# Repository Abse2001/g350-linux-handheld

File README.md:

# G350 AM3352 Linux handheld — in progress

**Cloud continuation:** start with [the complete handoff](docs/CLOUD_HANDOFF.md),
[the original user-visible chat](docs/CHAT_CONTEXT.md) and [AGENTS.md](AGENTS.md).
The full authored project and hash-indexed ignored routing evidence are preserved;
restore with `python3 scripts/restore-cloud-evidence.py`. Ubuntu cloud setup is
`bash scripts/setup-cloud.sh`, followed by `source cloud/env.sh` in each shell.
The checked default is still the eleven-signal byte0 subset. Latest byte1 source
replays and native failures are preserved separately; their aggregate/remaining
independent checks are pending. This transfer does not make the PCB order-ready.

The selected processor is a **bare TI AM3352BZCZ100**, directly on the main PCB, with **512 MB Micron MT41K256M16TW-107:P DDR3L** operated in DDR3-compatible mode. The user chose AM3352 for simple games rendered by the CPU; a 3D GPU is no longer required. The design is authored in **tscircuit**, using individually imported JLCPCB components. No complete SBC or processor module is imported.

**The integrated handheld is not ready to fabricate or order.** The current checked routing entry is [`experiments/am3352-g350-byte0-complete-bus.circuit.tsx`](experiments/am3352-g350-byte0-complete-bus.circuit.tsx): **280 placed components, four copper layers, a 76 × 118 mm shaped outline and 1.6 mm nominal thickness**. The lower speaker tab is 22 mm wide with a 19 mm extension. This routing entry and its CPU/RAM power replay both match the shared mechanical geometry; run `node scripts/check-g350-mechanical-envelope.mjs` to check them. These are provisional dimensions inside the published exterior envelope; mounting posts, shell ribs and button/port alignment remain unmeasured. The default `index.circuit.tsx` now opens this current shaped handheld. Older 212-component routing fixtures remain historical experiments; their channel counts do not qualify this layout. DDR and other critical routing, Linux provisioning and original-shell fit remain unfinished. The fabrication exporter remains blocked by `design-status.json`.

On the current shaped board, **all 101 CPU/RAM ground and DDR supply terminals** reach their correct filled reference planes through 97 physical vias. **All eleven byte0 signals** use native `bus_lanes` carriers and manually repaired routes, with their complete source-bus definition restored. Byte0 planar skew is **0.207792 mm against 0.635 mm**; strobe-pair skew is effectively zero against 0.127 mm. Numeric-pad connectivity, all-layer Gerber shorts and independent physical DRC pass for this subset. The source has **112 traces and 119 standard through-vias**. There are **38 DDR signals to route**, 403 silkscreen warnings, 818 open-port errors and 108 missing-trace errors. Bypass loops, complete timing and stackup impedance remain unqualified. [Current routing checks](checks/integrated/g350-byte0-complete-bus/check-summary.json), [bottom snapshot](checks/integrated/g350-byte0-complete-bus/g350-byte0-bottom.png), [routing notes](docs/G350_CURRENT_DDR.md). The separate byte1 experiment now has 22 manual package escapes with zero native geometry errors. Its native `bus_lanes` carrier attempt exhausted the strobe-pair search budget; the actual-source fanout replay returned the cached escapes but its implicit completion stage exceeded the external deadline. No completed byte1 source or new connected signals are qualified; the checked default is preserved. [Experimental findings](checks/integrated/g350-ddr-bootstrap/byte1-package-access-findings.json).

The completed handheld must have eleven front buttons, an FPC display, an onboard microSD holder and one USB-C connector for charging and data/provisioning. Components and copper routing are allowed on both sides. There are no analog sticks or rear buttons.

The historical command package-access study independently verifies **all 48 CPU/RAM pad-to-via exits for the 24 command/control signals**, while retaining both data bytes, reset and the clock pair. Shorts, copper/drill clearance and filled RAM reference checks pass. The diagnostic has 25 retained complete DDR channels, 48 dangling terminal-via warnings and 24 unfinished commands. Subsequent phased native routing plans six carriers; manual repair plans five more, leaving 13 unresolved. These carriers still need a combined editable replay and independent checks. The best checked complete-signal subset remains DDR42. [Package-exit evidence](checks/integrated/am3352-command-compatible-fanouts-802-check-summary.json). Fabrication remains blocked; no remote publication was made.

The latest separate **DDR42 checkpoint connects 42/49 DDR signals**, with 144 trace pieces and 187 full-depth through-vias. Independent numeric-pad connectivity, all-layer Gerber shorts and physical clearance/drill checks pass. Both byte groups and all three differential pairs pass relative planar skew. **Seven signals remain open:** A3, RASn, WEn, A2, A12, A11 and CKE. Seventeen command/clock nominal lengths and seven reduced-spacing exposures need repair; complete DDR timing and signal integrity remain unqualified. The updated `bus_lanes` phase preserves the fixed copper and physical pads but has no complete new output. [Checked evidence](checks/integrated/am3352-command-fine-782-replay-check-summary.json), [editable replay](experiments/am3352-command-fine-782-replay.circuit.tsx), [native phase entry](experiments/am3352-command-fine-782-replay-native-phase.circuit.tsx). At that historical checkpoint the default stayed DDR30; fabrication remains blocked.

The previous spacing-repaired **copper checkpoint connects 33/49 DDR signals**, with 135 trace pieces and 169 through-vias. A guarded wire-only D12 shortcut repairs its reduced class-spacing exposure from **32.176112 mm to 28.195190 mm**, within the **31.75 mm allowance**, without changing any holes or other routes. D12 is **50.983197 mm**; byte0/byte1 relative skews are **0.157421/0.496669 mm** and all three pairs retain their relative limits. Fresh native DDR/USB/filled-reference connectivity, all-layer Gerber shorts and physical DRC pass, with 418 presentation warnings, 499 reported/capped host opens and recorded ignored checks. **Sixteen DDR signals remain open**; CK/CKn/CKE/A3/A6 nominal repairs and complete spacing, impedance, return-path, termination and timing qualification remain required. [Checked copper](checks/integrated/am3352-ddr-usbc-d12-spacing-repaired-check-summary.json), [partial spacing audit](checks/integrated/am3352-ddr33-d12-repaired-class-spacing.json), [top](images/am3352-ddr-usbc-d12-spacing-repaired-top.png) and [bottom](images/am3352-ddr-usbc-d12-spacing-repaired-bottom.png). Revalidate with `npm run check:ddr-d12-spacing-evidence` and `npm run check:ddr-class-spacing`. That historical checkpoint retained the 30/49 default; fabrication remains blocked.

A separate **bottom-side RAM placement study** retains all 212 host components, 912 pads and 49 logical DDR connections. RAM references and shared USB-C copper pass fresh independent checks on four layers; fourteen small RAM bypass capacitors move to top, and all 89 existing holes remain standard 18/10 mil through-vias. DDR is entirely unrouted in this study. Native all-channel and ordered-fanout trials **704–709** prepare real endpoints but have no complete output; no partial routes are promoted. An initial eight-USB-via size failure is retained as rejected evidence, followed by a corrected, checked rebuild. [Placement checks](checks/integrated/am3352-ram-bottom-via-style-corrected-check-summary.json), [seven bound terminal trials including D12 repair 703](checks/integrated/am3352-ddr33-d12-ram-bottom-trial-status.json). Revalidate with `npm run check:ram-bottom-evidence` and `npm run check:ddr-d12-ram-bottom-trials`.

The newer bottom-RAM replay has **28/49 connected DDR signals**, comprising **19 retained native bus-lane paths and nine manual paths**. All original 102 host/USB/reference trace pieces and 89 physical holes remain exact; this candidate has 130 trace pieces and 129 through-vias. Independent numeric-pad DDR/USB and filled-reference connectivity, all-layer shorts and physical DRC pass. **21 DDR signals remain open**, both byte groups are incomplete, and command matching/nominal lengths remain unqualified. Its separate placement-derived command target is **40.62 mm**; this does not change the top-RAM target. All 28 connected paths pass the partial reduced-spacing exposure limit, with a maximum of 31.421059 mm; complete spacing and signal integrity remain unchecked. A selected-terminal-via search-model bug was corrected and regression checked. The unsolved native run is retained as provenance, rather than represented as a solved 49-channel output. [Checked replay](checks/integrated/am3352-ram-bottom-flexible-fanout-747-replay-check-summary.json), [electrical review](checks/integrated/am3352-ram-bottom-flexible-fanout-747-replay-spacing-and-nominal-review.json), [38 terminal trials](checks/integrated/am3352-bottom-manual-trial-status.json), [top](images/am3352-ram-bottom-flexible-fanout-747-replay-top.png) and [bottom](images/am3352-ram-bottom-flexible-fanout-747-replay-bottom.png). That historical study retained the 30-signal default and separate 33-signal checkpoint. Nothing was pushed or released for ordering.

The earlier **A6 copper bootstrap connects 32/49 DDR signals** in one source, with 134 trace pieces and 163 through-vias. It supplies the checked prior geometry for the CASn replay. Its A6=51.715840 mm and A3=45.411583 mm nominal failures remain required repairs. [Prior scoped checks](checks/integrated/am3352-ddr-usbc-a6-bootstrap-check-summary.json); `npm run check:ddr-a6-bootstrap-evidence`.

The earlier **A3 copper bootstrap connects 31/49 DDR signals**, with 133 trace pieces and 161 through-vias. It preserves every checked DDR30 trace and hole. Native DDR/USB/reference connectivity, all-layer shorts and physical DRC pass, but **A3=45.411583 mm fails the nominal range**. The wire-only shortcut search could not bring it into range. This checkpoint supplies the checked prior copper for the separate A6 replay. [A3 bootstrap checks](checks/integrated/am3352-ddr-usbc-a3-bootstrap-check-summary.json). Revalidate with `npm run check:ddr-a3-bootstrap-evidence`.

Earlier DQM1/D10 access trials routed native CASn and CSn0 but could not restore the two data routes. Those incomplete stages remain non-exportable and are superseded by the complete D3-coupled replay above. [Historical bound trials](checks/integrated/am3352-ddr32-casn-neighbor-replan-trial-status.json); `npm run check:ddr-casn-neighbor-replan-trials`.

The board must **fit the original G350 shell**. Its listed 81 × 128 × 22 mm outside dimensions do not establish the internal PCB outline. The working G350 outline is **76 × 118 mm**, with chamfered corners and a lower speaker tab; see the [dimensioned drawing](mechanical/g350-provisional-outline.svg). The nominal centered margins from the outside case are 2.5 mm per side and 5 mm per end; the USB-C assembly courtyard projects 0.651 mm past the top PCB edge. These are engineering allowances, not measured internal clearances or a verified original-board replacement. The historical 100 × 124 mm routing fixture does not fit the case and is not the mechanical target. Original screw posts, button centers, port openings and assembly clearances still require verification. [Shell-fit requirements](docs/G350_SHELL_FIT.md).

The historical DDR30 default was `experiments/am3352-ddr-usbc-wen-nominal.circuit.tsx`: **30/49 DDR signals connected**, with **132 trace pieces and 157 through-vias**. A native `bus_lanes` WEn carrier inside the DDR reference bounds and guarded manual package fanouts give **WEn=43.228641 mm**, within the placement-derived 41.75–44.29 mm nominal range. Every checked DDR29 trace and hole remains unchanged. A5 remains **43.020000 mm**, CSn0 **42.800714 mm**, ODT **43.018281 mm** and D14 **50.919109 mm**. Both bytes and all three differential pairs retain their checked relative planar limits. Exact native DDR/USB/reference connectivity passes, with zero all-layer Gerber shorts and reported physical DRC violations, 418 presentation warnings and 499 reported/capped host opens. All 18 RAM supply balls, 21 ground balls and 28 bypass terminals reach the connected filled reference planes. Configured ignored native checks remain recorded. CKE/clock nominal lengths still fail; the **19 remaining address/control signals**, full command matching, package/via delays, coupling/impedance, powered host/Linux and original-shell fit remain unqualified. [Checked evidence](checks/integrated/am3352-ddr-usbc-wen-nominal-check-summary.json); [top](images/am3352-ddr-usbc-wen-nominal-top.png) and [bottom](images/am3352-ddr-usbc-wen-nominal-bottom.png) snapshots. Revalidate with `npm run check:ddr-wen-evidence`. Earlier candidates below are historical evidence.

The historical DDR28 replay is `experiments/am3352-ddr-usbc-csn-joint.circuit.tsx`: **28/49 DDR signals connected**, with **130 trace pieces and 149 through-vias**. A native `bus_lanes` CSn0 carrier and guarded manual package fanouts add **CSn0 at 42.800714 mm**, within the placement-derived 41.75–44.29 mm nominal range. D10 remains unchanged; only D14's CPU prefix is repaired with two vias, giving **D14=50.919109 mm**. All 147 old holes and the other 128 traces remain unchanged. Byte0/byte1 skews remain **0.157421/0.635000 mm**; DQS1/CK skews remain **0.079409/0.076616 mm** against 0.127 mm. Exact native DDR/USB/reference connectivity passes, with zero all-layer Gerber shorts and reported physical DRC violations, 418 presentation warnings and 499 reported/capped host opens. All 18 RAM supply balls, 21 ground balls and 28 bypass terminals reach the connected filled reference planes. The configured ignored native checks remain recorded. CKE/clock nominal lengths still fail; the **21 remaining address/control signals**, complete command matching, package/via delays, coupling/impedance, powered host/Linux and original-shell fit remain unqualified. [Checked evidence](checks/integrated/am3352-ddr-usbc-csn-joint-check-summary.json); [top](images/am3352-ddr-usbc-csn-joint-top.png) and [bottom](images/am3352-ddr-usbc-csn-joint-bottom.png) snapshots. Revalidate with `npm run check:ddr-csn-evidence`.

The historical unmatched **26/49 DDR continuity candidate** adds CKE using a native bus_lanes channel and manually repaired RAM fanouts. All exact DDR/USB and RAM reference connections pass, with zero all-layer shorts and physical DRC violations. A bounded DDR power-plane clearance change restores the RAM supply island while preserving manufacturing minimums and plane boundaries. **DQS1 and byte1 skew still fail at 10.167587/10.584847 mm**, and CKE is longer than the current placement-derived nominal range. This earlier candidate remains separate from the repaired default. [Scoped evidence](checks/integrated/am3352-ddr-usbc-cke-joint-power-plane-bounded-check-summary.json); [top](images/am3352-ddr-usbc-cke-joint-power-plane-bounded-top.png) and [bottom](images/am3352-ddr-usbc-cke-joint-power-plane-bounded-bottom.png) snapshots. Revalidate with `npm run check:ddr-cke-joint-plane-evidence`.

The historical separate **25/49 DDR continuity trial** restores both strobes around a freshly routed native `bus_lanes` clock pair. All 25 exact CPU/RAM pad pairs, shared USB-C copper and RAM plane/bypass connections pass independent checks, with zero physical DRC violations and all-layer Gerber shorts. The clock pair passes its 0.127 mm planar limit at **0.076616 mm**. **Strobe and whole-byte1 matching still fail at 7.145626 mm**; strobe via counts are also unequal. This 127-trace/137-via trial does not replace the checked default. Its 24 address/control signals, full electrical timing, complete host and measured original-shell layout remain unfinished. [Scoped checks](checks/integrated/am3352-ddr-usbc-clock-strobes-unmatched-check-summary.json); [editable source](experiments/am3352-ddr-usbc-clock-strobes-unmatched.circuit.tsx); [top](images/am3352-ddr-usbc-clock-strobes-unmatched-top.png) and [bottom](images/am3352-ddr-usbc-clock-strobes-unmatched-bottom.png) snapshots. Revalidate with `npm run check:ddr-strobe-evidence`.

The newest coordinated diagnostic preserves eleven byte0 channels and independently verifies all **74 remaining byte1/command escape terminals** around them. All-layer shorts and clearance violations are zero, and RAM plane connections pass. Those reservations add no complete channels; byte0 length matching still fails, and dangling copper remains. The separately matched byte1 candidate has not been merged. [Combined reservation checks](checks/integrated/am3352-ram-rotated-180-byte0-fixed-reused-reservations-check-summary.json).

A newer whole-byte-swap alternative routes all eleven byte0 channels with **24 DDR vias**. Independent pad/plane connectivity, shorts and physical DRC checks pass, but whole-byte skew still fails at 13.889 mm against 0.635 mm. Native preparation can reserve the remaining 74 terminals around that copper; byte1 routing remains incomplete. This separate candidate does not replace or add channels to the default layout. [Swapped-byte checks](checks/integrated/am3352-ram-rotated-180-byte-swapped-byte0-pair-check-summary.json).

A separate **212-component USB-C source draft** now adds the shared charging/data socket, USB0 ESD protection, independent CC pull-downs and a VBUS sensing filter/clamp. Generated connections and all 36 exported USB numeric-pad assignments pass. Its existing eleven DDR channels and RAM plane connections pass fresh native checks; shorts and physical DRC violations are zero. **USB traces, charger current policy, VBUS temperature/transient limits and Linux provisioning remain unfinished**, along with the measured original-shell layout. No finished board was imported. [USB-C checks](checks/integrated/am3352-usbc-device-check-summary.json); source: `experiments/am3352-usbc-device-source.circuit.tsx`.

The newer **USB copper replay** routes data from the CPU through ESD protection to both connector orientations, both CC/Rd connections, local VBUS bypass and ground returns. Native `bus_lanes` supplies the pair/CC bootstrap; manual connections and tuning supplement it. Fresh source, KiCad connectivity, physical DRC and all-layer shorts checks pass. Both data orientations have **0.0635 mm planar skew**, with equal via counts within each orientation. The replay adds 23 trace pieces and 12 through-vias while preserving its eleven DDR channels. **The PMIC VBUS feed, CPU VBUS sensing, controlled impedance, current policy, remaining DDR/host routing, Linux provisioning and shell fit remain unfinished.** This candidate remains separate from the default 23-channel DDR source. [Routed USB checks](checks/integrated/am3352-usbc-routed-check-summary.json), [editable source](experiments/am3352-usbc-routed-replay.circuit.tsx), [PCB snapshot](images/am3352-usbc-routed-top.png).

## DDR routing workflow

The [tscircuit DDR routing guide](https://docs.tscircuit.com/guides/routing-ddr) was rechecked on 2026-10-04, including the complete AM3352 example. The native preset is `autorouter="bus_lanes"`. The default circuit uses this preset to generate local dogbones and route the channel. Manual fanouts, placement changes and local trace repairs may supplement it when needed; successful copper still requires independent checks.

The new fixture declares **49 actual shared DDR signals**, two 11-signal byte buses, a 26-signal command/clock timing group, and separate reset. It declares both DQS differential pairs and the CK pair. The 4 Gb x16 memory uses A0–A14; its M7 is NC. CPU DDR_A15 is therefore unused. Numeric port selectors avoid collisions between RAM ball labels such as A3 and address-function aliases with the same name.

All **324 CPU and 96 RAM balls**, functions and nominal 0.8 mm grids have been checked against the manufacturer documents. The supplier import's incomplete CPU aliases and malformed RAM aliases were corrected. CPU pads use TI's 0.4 mm example lands; RAM pads use the Micron TW drawing's 0.42 mm lands. This is a nominal geometry/function check, not complete solder-mask or assembly qualification. See `checks/integrated/am3352-import-validation.json`.

The historical repaired-strobe source connects **25/49 DDR signals**: both complete byte lanes, reset and CK/CKn. Byte0 uses bottom, byte1 top, and inner1 GND/inner2 DDR power remain reference planes. Manual RAM strobe escapes supplement the native bootstrap. Removing a redundant inward CPU/channel turn shortens DQS1 from 53.720144 to 50.953139 mm; DQSn1 is 51.001321 mm. Every other route of the checked clock source remains unchanged. Both bytes, both DQS pairs and CK pass their separate planar limits, while the complete command/clock group correctly fails because its 24 address/control signals are open. All 25 exact CPU/RAM pad pairs are independently verified in KiCad. This does not qualify full electrical timing or fabrication.

A separate fresh native bootstrap now reserves all **96 CPU/RAM breakouts for all 48 synchronous DDR signals together**, retaining the original power copper and four-layer limit. KiCad verifies all 96 pad-to-via connections and the RAM plane/bypass connections. Gerber shorts and clearance errors are zero; all 96 unfinished-via warnings remain. This creates no new complete channel and does not replace the checked 23-signal default. [Joint breakout checks](checks/integrated/am3352-joint-native-breakout-check-summary.json).

The next separate trial has **all 52 natural command/clock fanouts connected to their exact CPU/RAM pads**, with zero all-layer shorts and clearance errors. Its 47 dangling-via and 44 dangling-track warnings remain. [Natural fanout checks](checks/integrated/am3352-natural-command-fanouts-check-summary.json).

A terminal-via diagnostic also passes all 52 pad-to-terminal checks with zero all-layer shorts and clearance violations. It retains 96 dangling-via warnings and completes no new DDR channel. The current repair uses only four added clock-terminal vias, the native `bus_lanes` clock bootstrap and temporary manual bridges on top/bottom. Command-bus crossings and original timing limits must pass before accepting any routes. [Terminal checks](checks/integrated/am3352-dual-layer-command-terminal-check-summary.json).

The separate command/clock replay now connects **all 26 command signals**. Native `bus_lanes` supplies the bootstrap and two clock channels; manual fanout/channel repairs and A2 loop cleanup supplement it. The actual tscircuit source passes all-layer shorts and independent KiCad pad connectivity, RAM reference connectivity and physical DRC at every severity. It has 95 trace pieces and 199 through-vias. **Length matching still fails:** command skew is 53.182 mm against 0.635 mm, and clock skew is 2.898 mm against 0.127 mm. Its two bytes and reset are open. A merge screen finds five via/hole conflicts with the active byte routes, so these separate results do not make a 49-signal DDR board. [Command checks](checks/integrated/am3352-command-unmatched-pruned-check-summary.json), [editable replay](experiments/am3352-command-unmatched-pruned-replay.circuit.tsx).

The newer command-first diagnostic verifies all **44 native CPU/RAM byte breakouts** against that command copper, with zero all-layer shorts and clearance violations. It preserves all 26 command channels but adds no complete byte channel. Its 22 dangling-via and 22 dangling-track warnings remain. A separate local-access trial opens WEn, RASn and ODT to plan compatible byte routing; those nets still require complete rerouting and matching. [Byte-breakout checks](checks/integrated/am3352-command-first-native-byte-check-summary.json).

An earlier placement trial rotates RAM by **180°**, with explicitly transformed and checked supply escapes. Its joint native bootstrap verifies all 96 synchronous pad-to-terminal connections and preserves all 39 RAM supply/ground and 28 bypass-plane connections. The pruned reservation retains 74 dangling-via and 22 dangling-track warnings and adds no complete channel. [Rotated breakout checks](checks/integrated/am3352-ram-rotated-180-pruned-breakout-check-summary.json).

A separate editable replay of that placement now connects **all eleven byte0 signals through native `bus_lanes` channels and manual fanouts**. Actual tscircuit and KiCad checks confirm zero all-layer shorts, zero physical DRC violations, and preserved RAM plane connections. DQS skew is zero, but whole-byte skew is **16.105 mm against 0.635 mm**. It has 80 trace pieces and 99 through-vias; 38 DDR signals remain open. This candidate is separate from the active 23-signal layout, and routes from the old RAM orientation cannot be combined with it. [Rotated byte0 checks](checks/integrated/am3352-ram-rotated-180-byte0-pair-check-summary.json), [editable replay](experiments/am3352-ram-rotated-180-byte0-pair-replay.circuit.tsx).

## Build and verify

Versions reverified against the registry on 2026-10-05: **tscircuit 0.0.2744**, **tsci CLI 0.1.2237**, **capacity-autorouter 0.0.958**, and **core 0.0.2088**, **props 0.0.687** and **checks 0.0.239**. The project pins one core version, Circuit JSON 0.0.515 and React 19.3.0 so clean installs load compatible peers. Both lockfiles are synchronized; use `bun install --frozen-lockfile` or `npm ci --legacy-peer-deps`. The selected byte0 phase completes and typechecking and all-layer Gerber shorts pass. The whole-board build still reports its unfinished connections. The latest core audit preserves all physical records outside the explicitly reviewed D3 bend and sub-picometre handoff-coordinate repairs, and restores all eleven byte0 bus members. Previously checked circuit/board files remain fixed evidence. [Current upgrade and source checks](checks/integrated/g350-byte0-complete-bus/core-upgrade-and-bus-check.json).

Run direct CLI commands with **`node_modules/.bin/tsci`**; npm scripts already select the project binary. The shell's older global `tsci` reports runtime 0.0.2444 and omits the microSD keepouts in KiCad exports. Affected new exports and shorts checks were rerun with the project CLI. Latest-project-CLI builds reproduce every non-metadata record of both new clock/strobe replays; frozen earlier source snapshots remain intact.

```sh
npm ci --legacy-peer-deps
npm run typecheck
npm run check:am3352-imports
npm run check:am3352-swizzle
npm run build:host-netlist
npm run check:power-netlist
npm run check:boot-netlist
npm run check:storage-netlist
node_modules/.bin/tsci build index.circuit.tsx --disable-parts-engine --autorouter-phase G350_BYTE0_MATCHED --autorouter-timeout 180s
npm run check:memory-connectivity
npm run check:shorts
```

The legacy peer option is required by the current upstream packages' circuit-json peer versions. All-layer Gerber shorts, full signal connectivity, end-to-end skew measurements and independent KiCad copper/drill checks must be run on actual exported AM3352 copper. The completed handheld requires fresh checks after power and peripherals are integrated.

`build:host-netlist` disables automatic routing. Source audits accept only the exact documented package reference escapes and bypass loops, including same-net drill separation; they do not approve arbitrary copper. The checks cover voltage domains, power/reset controls, internal-output isolation, DDR VREF/VTP/ZQ, bypass placement, boot straps and the actual microSD pinout/keepouts. The current shaped-board DDR audit reports eleven connections and still fails on 38 open signals. The historical DDR30 audit fails on 19 open signals; the latest separately checked DDR42 replay has seven opens and still fails command nominal lengths and reduced-class spacing. Both completed byte groups pass their relative planar and physical checks. Remaining host copper and full electrical qualification are unfinished. The partial physical summary rejects copper/drill violations even when KiCad reports them as warnings.

## Repositories and records

- [GitHub](https://github.com/Abse2001/g350-linux-handheld)
- [tscircuit: AM3352 experimental source v1.3.3](https://tscircuit.com/abse/g350-linux-handheld?version=1.3.3-integrated-experimental)
- [Current integrated-host record](docs/INTEGRATED_HOST.md)
- [Historical RK3566 host investigation](docs/RK3566_HOST_RECORD.md)
- [Historical RK3566 memory experiments](docs/RK3566_MEMORY_EXPERIMENTS.md)
- [Historical Revision B carrier](docs/REV_B_CARRIER.md)

Work remains local; GitHub and tscircuit are pushed only on a meaningful breakthrough, as requested. Registry publication is not fabrication approval. `tsci push` ignores `.gitignore`; use the tracked source allowlist in `scripts/stage-registry-source.mjs` and verify every published file hash. Reference PDFs, temporary files and historical manufacturing archives are excluded.

Historical RAM180 milestone: a separate RAM180 replay connects **all eleven byte1 signals**, using native `bus_lanes` channels and manually tuned local fanouts. Actual tscircuit and independent KiCad checks pass shorts, copper/drill clearance, correct numeric pad connectivity and every RAM supply/ground/bypass connection. Whole-byte planar skew is **0.000759 mm against 0.635 mm**, and strobe skew is effectively zero against 0.127 mm. This replay has 81 trace pieces and 111 through-vias. Its other 38 DDR signals remain open; full host routing, impedance, Linux startup and original-shell fit are unfinished. It is not order-ready. [Editable replay](experiments/am3352-ram-rotated-180-byte1-matched-replay.circuit.tsx), [checks](checks/integrated/am3352-ram-rotated-180-byte1-matched-check-summary.json), [snapshot](images/am3352-ram-rotated-180-byte1-matched-top-detail.png). Revalidate with `npm run check:rotated-byte1-matched-evidence`. Other candidate channel counts cannot be added to this result.

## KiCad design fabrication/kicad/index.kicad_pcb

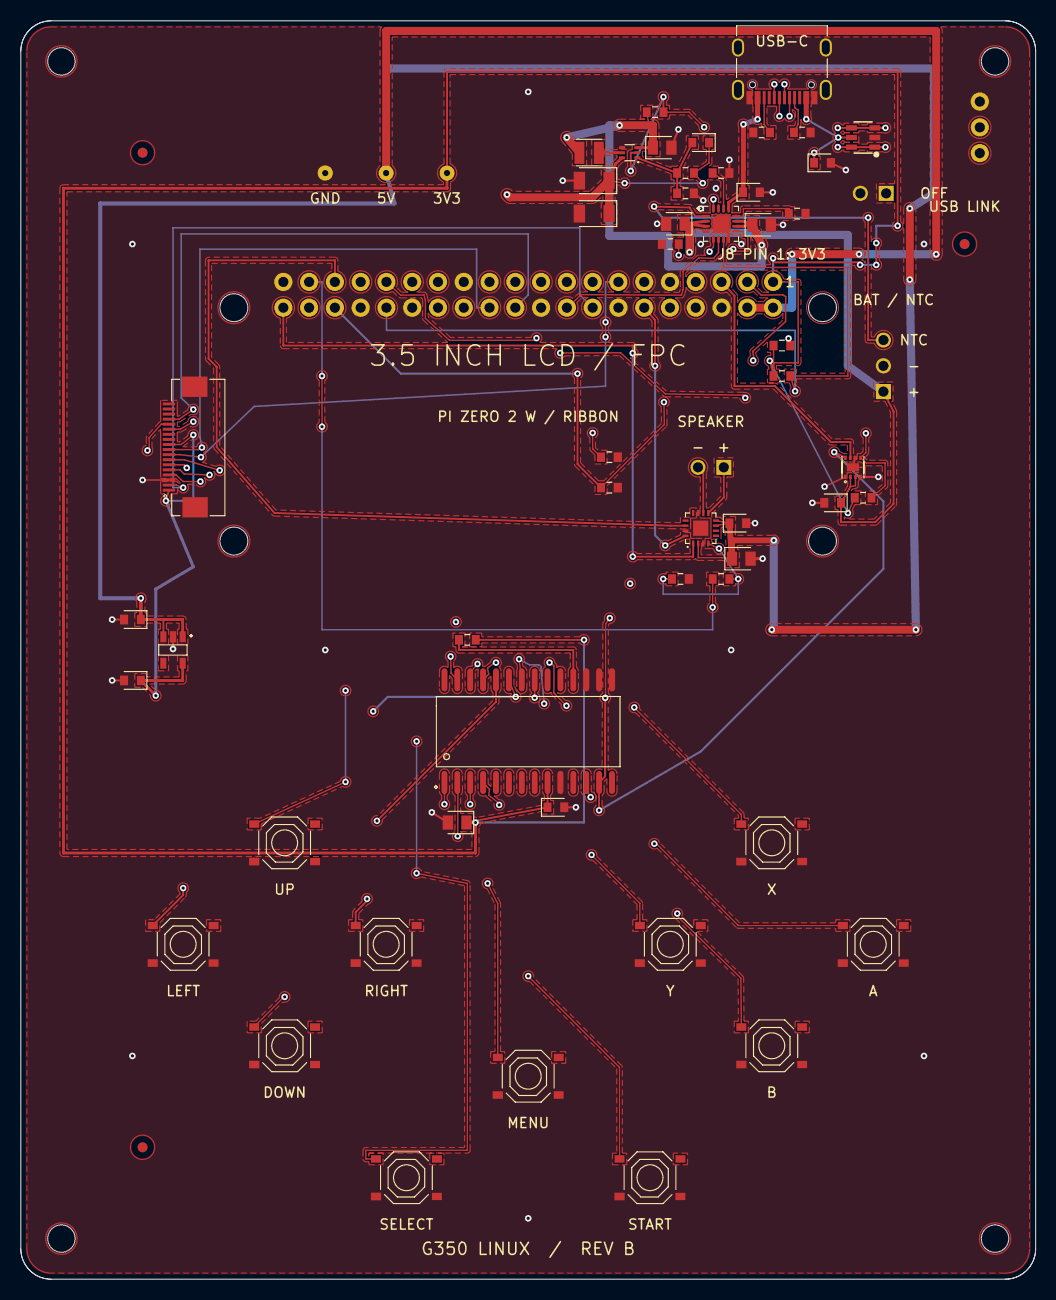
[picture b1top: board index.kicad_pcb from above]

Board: 4 copper layers, 100.0 x 124.0 mm, 60 parts (0 on the bottom side), 52 nets.

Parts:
C_AUDIO_BULK: 10uF; g350_C_AUDIO_BULK_6c8053e0121015ff486027e25d2f9a3d
C_AUDIO_HF: 100nF; g350_C_AUDIO_HF_4f8718706f1c09302dbf2ad0139db390
C_BAT: 10uF; g350_C_BAT_47d06ae03787dae1491fdf5e36386663
C_BOOST_IN: 10uF; g350_C_BOOST_IN_5255146047f73ebf3d99691e333b937d
C_BOOST_OUT1: 22uF; g350_C_BOOST_OUT1_7e38f91c406a288400f2b5dc424f943c
C_BOOST_OUT2: 22uF; g350_C_BOOST_OUT2_1b885d80651f5cbf1a38e902666ed13d
C_FEEDFORWARD: 220pF; g350_C_FEEDFORWARD_16c584a07135c2813459ff9e26163e43
C_GAUGE: 100nF; g350_C_GAUGE_07aee08077a9654108fe54fe7659f0c3
C_KEYS: 100nF; g350_C_KEYS_644960c23e17dcbe1f86e5c27d25a842
C_KEYS_BULK: 10uF; g350_C_KEYS_BULK_468ee6ca3a2664ea2dbde30a2155612a
C_LCD_IN: 1uF; g350_C_LCD_IN_5be2f4460c8d09ba74fd07ba2292fa46
C_LCD_OUT: 1uF; g350_C_LCD_OUT_796ff1802c1fd09f2e506d42773f54dd
C_SYS: 10uF; g350_C_SYS_08f8654077af54ff07a8f0c278fec97d
C_USB: 1uF; g350_C_USB_6f7d3200112a883f6e2dbd821279fcbd
C_USB_ESD: 100nF; g350_C_USB_ESD_55af1c004fe0a61f0a8f97c264ffd5a3
J_BAT: J_BAT; g350_J_BAT_1c1b67e03e54d601673aec1e0ccaae3d
J_LCD: FPC-05F-18PH20; g350_J_LCD_023284580e9b06381b038818276c09f8
J_OFF: J_OFF; g350_J_OFF_72356f40335a52df2715eb027e79d71d
J_PI: 2x20 2.54mm GPIO ribbon header; g350_J_PI_45b957de51d6aa22169953de7f0951de
J_SPEAKER: J_SPEAKER; g350_J_SPEAKER_3187528028e8eb617ca6d6be223698dd
J_USB: TYPE-C-31-M-12; g350_J_USB_2a17ef222ac30dde7f9e0ade2b86f822
J_USB_LINK: J_USB_LINK; g350_J_USB_LINK_151b40200abd6a7f005f94de09fe40c3
L_BOOST: 1µH; g350_L_BOOST_162d00c0709d3ea134f2837e257dba63
R_ALERT_PULL: 100kΩ; g350_R_ALERT_PULL_3ed784801b98b9617608f7422f86cadd
R_AUDIO_EN: 1kΩ; g350_R_AUDIO_EN_00256ea05a4acf414b44f2de0f2b4b03
R_AUDIO_PD: 100kΩ; g350_R_AUDIO_PD_59fa59004b95691f0edad4c2694b12a3
R_CC1: 5.1kΩ; g350_R_CC1_1675a34070e5e12134a9e0fe25c65ce3
R_CC2: 5.1kΩ; g350_R_CC2_70956ae034fa573f2575e6a27fe62483
R_CHG_PULL: 100kΩ; g350_R_CHG_PULL_7cb2e42028dcddff31935fe273fc623d
R_EN: 100kΩ; g350_R_EN_2bedbaa0536a8b212d3d2f1e521b16a3
R_FB_HI: 732kΩ; g350_R_FB_HI_577e14c02929a57f562ea0422a7919fd
R_FB_LO: 100kΩ; g350_R_FB_LO_1fea8fa05f6db621213a041e5e1e41a3
R_GOOD_PULL: 100kΩ; g350_R_GOOD_PULL_2f2dc0202b427dc17a4d445e1fdd067d
R_ILIM: 3.3kΩ; g350_R_ILIM_21d596405ed223ff208621c26021987d
R_ISET: 3.3kΩ; g350_R_ISET_2238e4a07ca9228128e69f9e31899e43
R_RESET: 10kΩ; g350_R_RESET_1a8653a074f691813099309e29d70d43
R_TIMER: 68kΩ; g350_R_TIMER_7999bf001f29811f3b46bcc26a49055d
R_USB_EN1: 100kΩ; g350_R_USB_EN1_2d820ae02cee330178a18f1e1e31513d
R_USB_EN2: 100kΩ; g350_R_USB_EN2_18011b8072715961331e68be2751d523
SW_A: SW_A; g350_SW_A_69607ec017473b7f68110a421896affd
SW_B: SW_B; g350_SW_B_732329a00c351c2174729e1e0ae5a7a3
SW_DOWN: SW_DOWN; g350_SW_DOWN_66fbc8fa73644ada7fccccba73cab166
SW_LEFT: SW_LEFT; g350_SW_LEFT_093028fc1598aadc22012cbc2e69ae9c
SW_MENU: SW_MENU; g350_SW_MENU_4553bc603b53fddf440447e23ca3725d
SW_RIGHT: SW_RIGHT; g350_SW_RIGHT_2a1c1df636849fd642ed21b64f55a396
SW_SELECT: SW_SELECT; g350_SW_SELECT_69cf658e5d66e3ae50fe61ce4495dfee
SW_START: SW_START; g350_SW_START_4c2facc034780d7f4ae0384235c781fd
SW_UP: SW_UP; g350_SW_UP_0f36f6001b9f77e02807f9c034707ba0
SW_X: SW_X; g350_SW_X_35f9e5604aadd4df34aa70e24bfd495d
SW_Y: SW_Y; g350_SW_Y_59763d0027317d3f5826c8822880f1bd
TP_3V3: TP_3V3; g350_TP_3V3_7afe24202a919dff2fde9fe275b1223d
TP_5V: TP_5V; g350_TP_5V_19c1e4e0743222c1315d9f5e29129e83
TP_GND: TP_GND; g350_TP_GND_1bb7c0407627fe212f67c3fe2b0879e3
U_AUDIO: MAX98357AETE+T; g350_U_AUDIO_22ebc3c07d5c01a12833c07e323c7d63
U_BOOST: TPS61023DRLR; g350_U_BOOST_1f3f53c079af91a12be0307e2e900d63
U_CHARGE: BQ24074RGTR; g350_U_CHARGE_5486e04005e95da160599b824536269d
U_GAUGE: MAX17048G+T10; g350_U_GAUGE_1b637ee075d3bcc12fbc055e2ab43883
U_KEYS: MCP23017-E/SO; g350_U_KEYS_647741a01ae1042165c6b61e19918fa3
U_LCD_PWR: AP2112K-3.3TRG1; g350_U_LCD_PWR_6bb0e2e01140a4ff492f98e25c60293d
U_USB_ESD: USBLC6-2SC6; g350_U_USB_ESD_7ae7b8e0673f34e15396b0e23fee2ce3

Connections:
AMP_ENABLE: J_PI.37, R_AUDIO_EN.1
AMP_MODE: R_AUDIO_EN.2, R_AUDIO_PD.1, U_AUDIO.4
BAT_ALERT_N: J_PI.31, R_ALERT_PULL.2, U_GAUGE.5
BOOST_SW: L_BOOST.2, U_BOOST.5
BUTTON_LEFT: SW_LEFT.1, U_KEYS.23
BUTTON_MENU: SW_MENU.1, U_KEYS.3
BUTTON_SELECT: SW_SELECT.1, U_KEYS.1
BUTTON_UP: SW_UP.1, U_KEYS.21
CHARGE_ISET: R_ISET.1, U_CHARGE.16
CHARGING_N: J_PI.29, R_CHG_PULL.2, U_CHARGE.9
FB: C_FEEDFORWARD.2, R_FB_HI.2, R_FB_LO.1, U_BOOST.1
GND: C_AUDIO_BULK.2, C_AUDIO_HF.2, C_BAT.2, C_BOOST_IN.2, C_BOOST_OUT1.2, C_BOOST_OUT2.2, C_GAUGE.2, C_KEYS.2, C_KEYS_BULK.2, C_LCD_IN.2, C_LCD_OUT.2, C_SYS.2, C_USB.2, C_USB_ESD.2, J_BAT.2, J_LCD.3, J_LCD.19, J_LCD.20, J_OFF.2, J_PI.6, J_PI.9, J_PI.14, J_PI.20, J_PI.25, J_PI.30, J_PI.34, J_PI.39, J_USB.1, J_USB.2, J_USB.3, J_USB.4, J_USB.13, J_USB.14, J_USB_LINK.3, R_AUDIO_PD.2, R_CC1.2, R_CC2.2, R_FB_LO.2, R_ILIM.2, R_ISET.2, R_TIMER.2, R_USB_EN1.2, R_USB_EN2.2, SW_A.3, SW_B.3, SW_DOWN.3, SW_LEFT.3, SW_MENU.3, SW_RIGHT.3, SW_SELECT.3, SW_START.3, SW_UP.3, SW_X.3, SW_Y.3, TP_GND.1, U_AUDIO.3, U_AUDIO.11, U_AUDIO.15, U_AUDIO.17, U_BOOST.4, U_CHARGE.4, U_CHARGE.8, U_CHARGE.17, U_GAUGE.1, U_GAUGE.4, U_GAUGE.6, U_GAUGE.9, U_KEYS.10, U_KEYS.15, U_KEYS.16, U_KEYS.17, U_LCD_PWR.2, U_USB_ESD.2
I2S_BCLK: J_PI.12, U_AUDIO.16
I2S_DIN: J_PI.40, U_AUDIO.1
I2S_LRCLK: J_PI.35, U_AUDIO.14
J_SPEAKER.pin1 to U_AUDIO.OUTP: J_SPEAKER.1, U_AUDIO.9
J_SPEAKER.pin2 to U_AUDIO.OUTN: J_SPEAKER.2, U_AUDIO.10
J_USB.CC2 to R_CC2.pin1: J_USB.12, R_CC2.1
LCD_BL: J_LCD.2, J_PI.16
LCD_CS: J_LCD.9, J_PI.24
LCD_DC: J_LCD.7, J_PI.15
LCD_RESET: J_LCD.8, J_PI.13
R_CC1.pin1 to J_USB.CC1: J_USB.6, R_CC1.1
R_RESET.pin1 to U_KEYS.N_RESET: R_RESET.1, U_KEYS.18
SCL: J_LCD.13, J_PI.5, U_GAUGE.7, U_KEYS.12
SDA: J_LCD.14, J_PI.3, U_GAUGE.8, U_KEYS.13
SPI_MISO: J_LCD.6, J_PI.21
SPI_MOSI: J_LCD.5, J_PI.19
SPI_SCLK: J_LCD.4, J_PI.23
SW_A.pin1 to U_KEYS.GPA4: SW_A.1, U_KEYS.25
SW_B.pin1 to U_KEYS.GPA5: SW_B.1, U_KEYS.26
SW_DOWN.pin1 to U_KEYS.GPA1: SW_DOWN.1, U_KEYS.22
SW_RIGHT.pin1 to U_KEYS.GPA3: SW_RIGHT.1, U_KEYS.24
SW_START.pin1 to U_KEYS.GPB1: SW_START.1, U_KEYS.2
SW_X.pin1 to U_KEYS.GPA6: SW_X.1, U_KEYS.27
SW_Y.pin1 to U_KEYS.GPB3: SW_Y.1, U_KEYS.4
TOUCH_IRQ: J_LCD.15, J_PI.22
USB_5V: C_USB.1, C_USB_ESD.1, J_USB.15, J_USB.16, U_CHARGE.13, U_USB_ESD.5
USB_DN: J_USB.7, J_USB.9, J_USB_LINK.1, U_USB_ESD.1, U_USB_ESD.6
USB_DP: J_USB.8, J_USB.10, J_USB_LINK.2, U_USB_ESD.3, U_USB_ESD.4
USB_EN1: J_PI.18, R_USB_EN1.1, U_CHARGE.6
USB_EN2: J_PI.36, R_USB_EN2.1, U_CHARGE.5
USB_GOOD_N: J_PI.32, R_GOOD_PULL.2, U_CHARGE.7
U_BOOST.EN to R_EN.pin2: J_OFF.1, R_EN.2, U_BOOST.2
U_CHARGE.ILIM to R_ILIM.pin1: R_ILIM.1, U_CHARGE.12
U_CHARGE.TMR to R_TIMER.pin1: R_TIMER.1, U_CHARGE.14
U_CHARGE.TS to J_BAT.pin3: J_BAT.3, U_CHARGE.1
V3V3: C_KEYS.1, C_KEYS_BULK.1, J_PI.1, R_ALERT_PULL.1, R_CHG_PULL.1, R_GOOD_PULL.1, R_RESET.2, TP_3V3.1, U_KEYS.9
V5V: C_AUDIO_BULK.1, C_AUDIO_HF.1, C_BOOST_OUT1.1, C_BOOST_OUT2.1, C_FEEDFORWARD.1, C_LCD_IN.1, J_PI.2, J_PI.4, R_FB_HI.1, TP_5V.1, U_AUDIO.2, U_AUDIO.7, U_AUDIO.8, U_BOOST.6, U_LCD_PWR.1, U_LCD_PWR.3
VBAT: C_BAT.1, C_GAUGE.1, J_BAT.1, U_CHARGE.2, U_CHARGE.3, U_GAUGE.2, U_GAUGE.3
VSYS: C_BOOST_IN.1, C_SYS.1, L_BOOST.1, R_EN.1, U_BOOST.3, U_CHARGE.10, U_CHARGE.11
V_LCD3V3: C_LCD_OUT.1, J_LCD.1, J_LCD.10, U_LCD_PWR.5
